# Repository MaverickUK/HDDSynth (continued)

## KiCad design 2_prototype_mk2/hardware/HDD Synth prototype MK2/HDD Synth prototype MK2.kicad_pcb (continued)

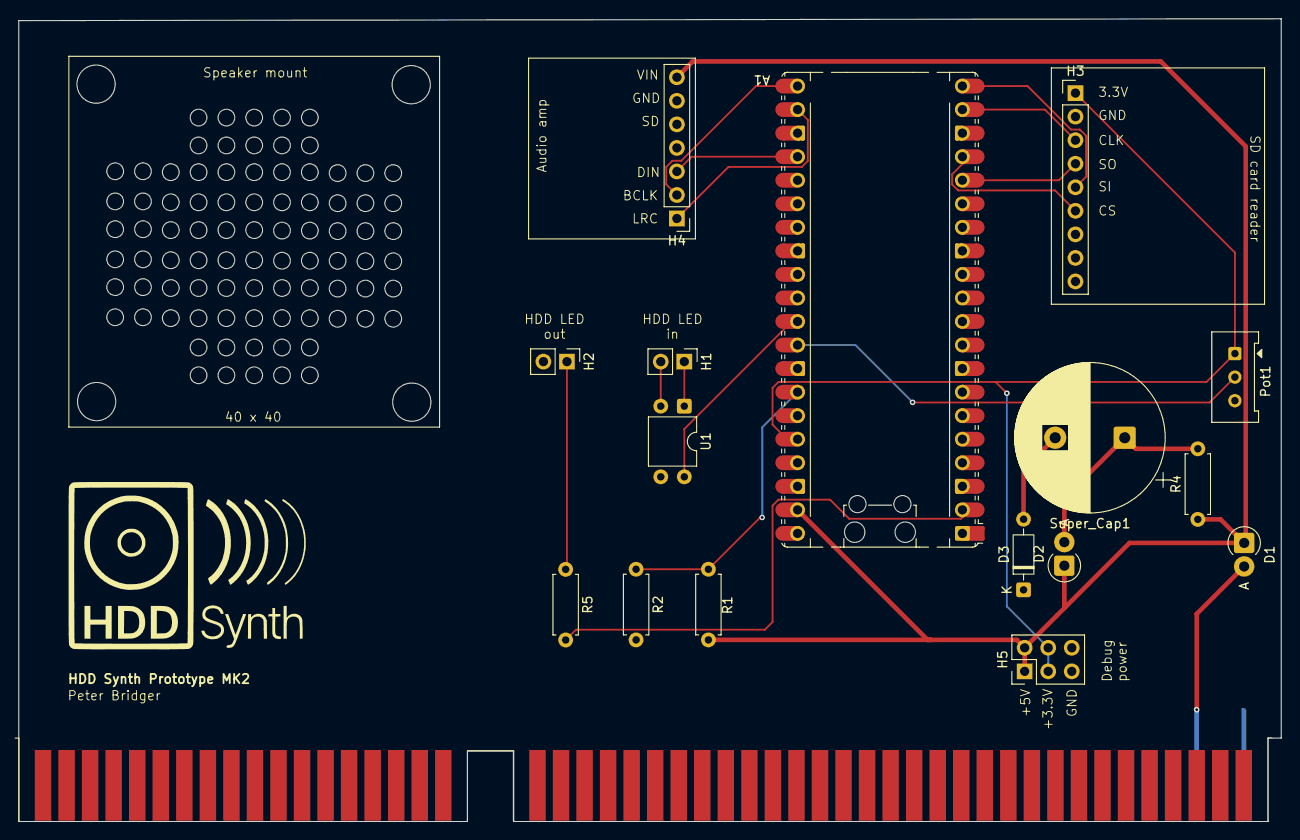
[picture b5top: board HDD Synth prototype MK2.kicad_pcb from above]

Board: 2 copper layers, 136.2 x 86.6 mm, 17 parts (0 on the bottom side), 19 nets.

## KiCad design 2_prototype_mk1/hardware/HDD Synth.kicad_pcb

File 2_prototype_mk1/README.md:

## HDD Synth
### Phase 2: PCB based prototypes

Phase 1 has established that this project is possible from both a hardware and software perspective. This phase is to create and iterate using a professionally manufactured PCB ready to enter phase 3, which will produce the released board.

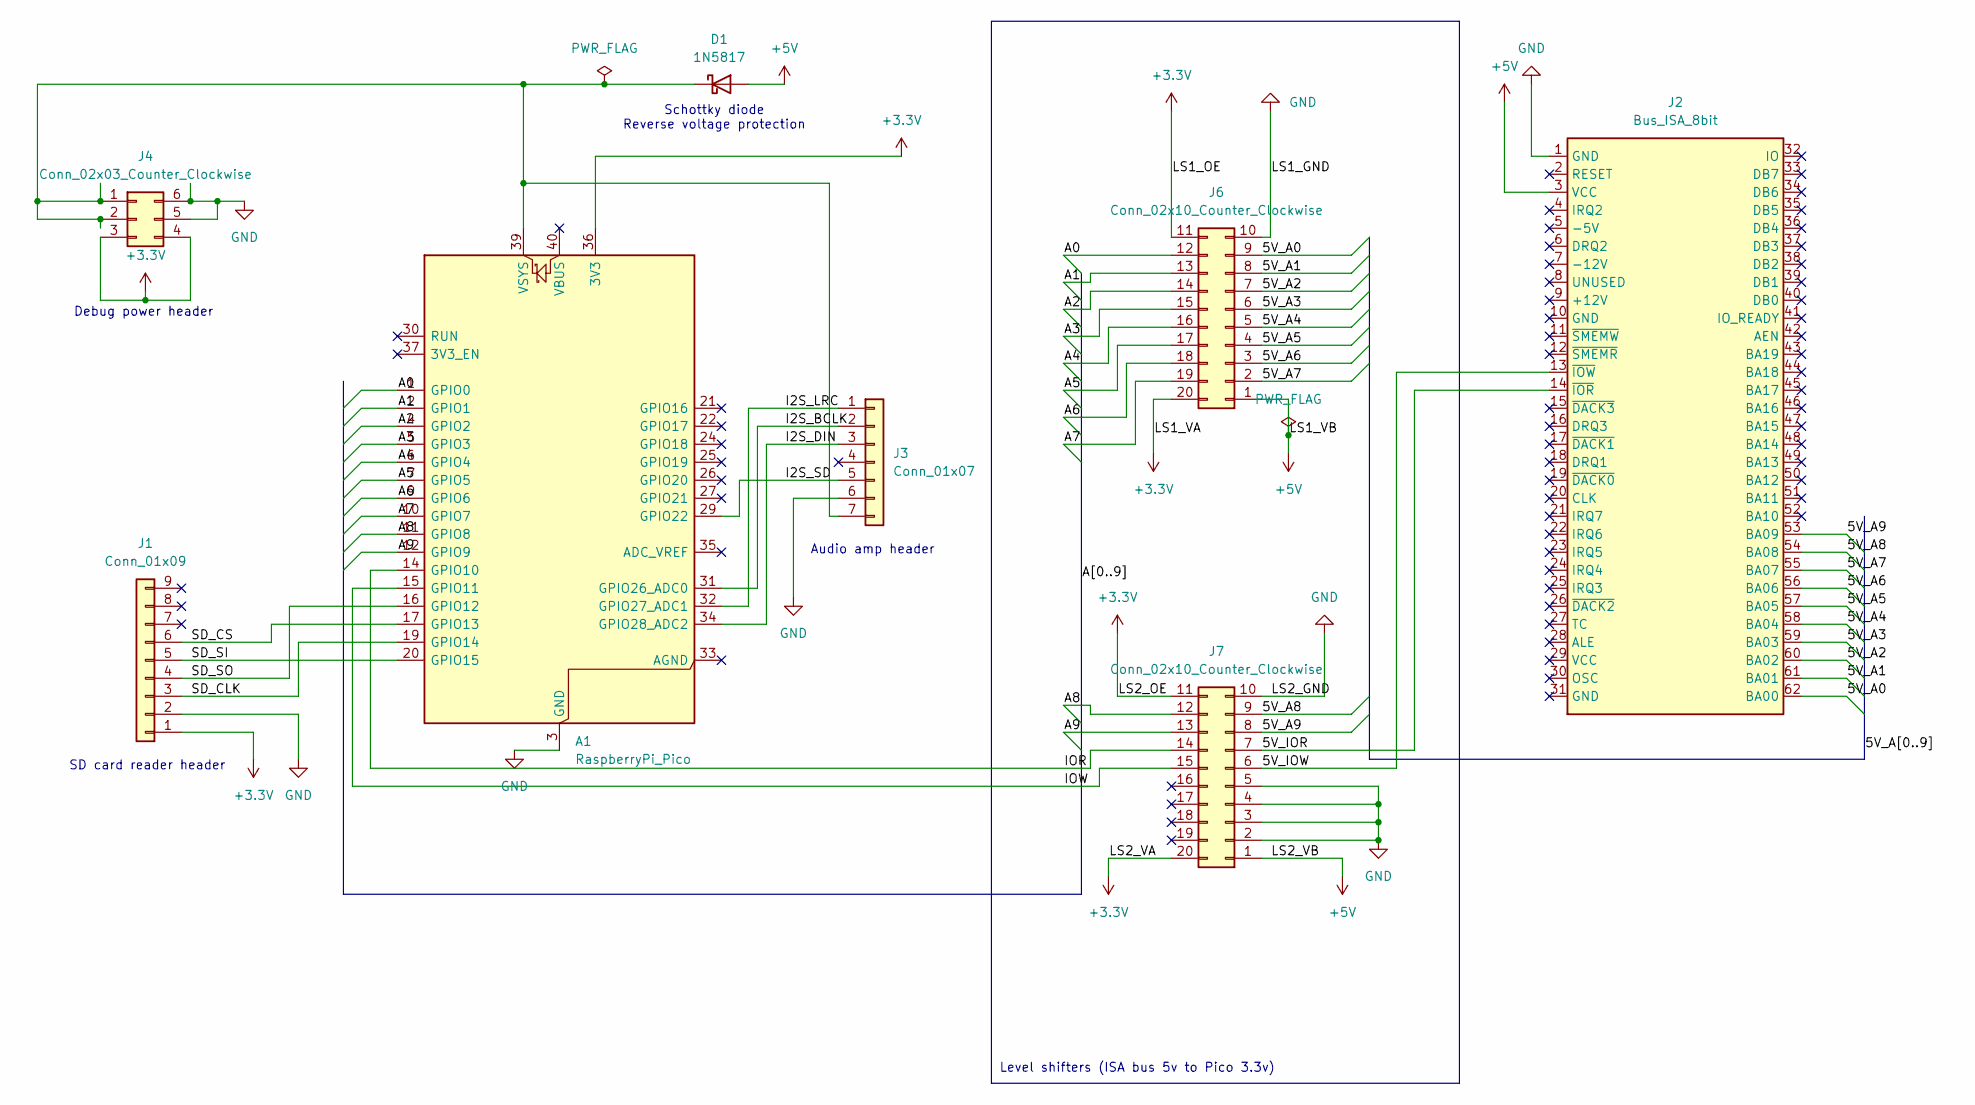
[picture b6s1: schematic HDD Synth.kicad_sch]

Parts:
A1: RaspberryPi_Pico; RaspberryPi_Pico_Common_Unspecified
D1: 1N5817; D_DO-41_SOD81_P2.54mm_Vertical_AnodeUp
J1: Conn_01x09; PinHeader_1x09_P2.54mm_Vertical
J2: Bus_ISA_8bit; BUS_AT
J3: Conn_01x07; PinHeader_1x07_P2.54mm_Vertical
J4: Conn_02x03_Counter_Clockwise; PinHeader_2x03_P2.54mm_Vertical
J6, J7: Conn_02x10_Counter_Clockwise; TXS0108E_2x10_Header2

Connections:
+3.3V: A1.36 (3V3), J1.1, J4.3, J4.4, J6.11, J6.20, J7.11, J7.20
+5V: D1.2 (A), J2.3 (VCC), J6.1, J7.1
/5V_A0: J2.62 (BA00), J6.9
/5V_A1: J2.61 (BA01), J6.8
/5V_A2: J2.60 (BA02), J6.7
/5V_A3: J2.59 (BA03), J6.6
/5V_A4: J2.58 (BA04), J6.5
/5V_A5: J2.57 (BA05), J6.4
/5V_A6: J2.56 (BA06), J6.3
/5V_A7: J2.55 (BA07), J6.2
/5V_A8: J2.54 (BA08), J7.9
/5V_A9: J2.53 (BA09), J7.8
/5V_IOR: J2.14 (~IOR), J7.7
/5V_IOW: J2.13 (~IOW), J7.6
/A0: A1.1 (GPIO0), J6.12
/A1: A1.2 (GPIO1), J6.13
/A2: A1.4 (GPIO2), J6.14
/A3: A1.5 (GPIO3), J6.15
/A4: A1.6 (GPIO4), J6.16
/A5: A1.7 (GPIO5), J6.17
/A6: A1.9 (GPIO6), J6.18
/A7: A1.10 (GPIO7), J6.19
/A8: A1.11 (GPIO8), J7.12
/A9: A1.12 (GPIO9), J7.13
/I2S_BCLK: A1.31 (GPIO26_ADC0), J3.2
/I2S_DIN: A1.34 (GPIO28_ADC2), J3.3
/I2S_LRC: A1.32 (GPIO27_ADC1), J3.1
/I2S_SD: A1.29 (GPIO22), J3.5
/IOR: A1.14 (GPIO10), J7.14
/IOW: A1.15 (GPIO11), J7.15
/SD_CLK: A1.19 (GPIO14), J1.3
/SD_CS: A1.17 (GPIO13), J1.6
/SD_SI: A1.20 (GPIO15), J1.5
/SD_SO: A1.16 (GPIO12), J1.4
GND: A1.3 (GND), A1.8 (GND), A1.13 (GND), A1.18 (GND), A1.23 (GND), A1.28 (GND), A1.38 (GND), J1.2, J2.1 (GND), J3.6, J4.5, J4.6, J6.10, J7.2, J7.3, J7.4, J7.5, J7.10
unnamed: A1.39 (VSYS), D1.1 (K), J3.7, J4.1, J4.2

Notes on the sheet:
Debug power header
SD card reader header
Level shifters (ISA bus 5v to Pico 3.3v)
Schottky diode Reverse voltage protection
Audio amp header

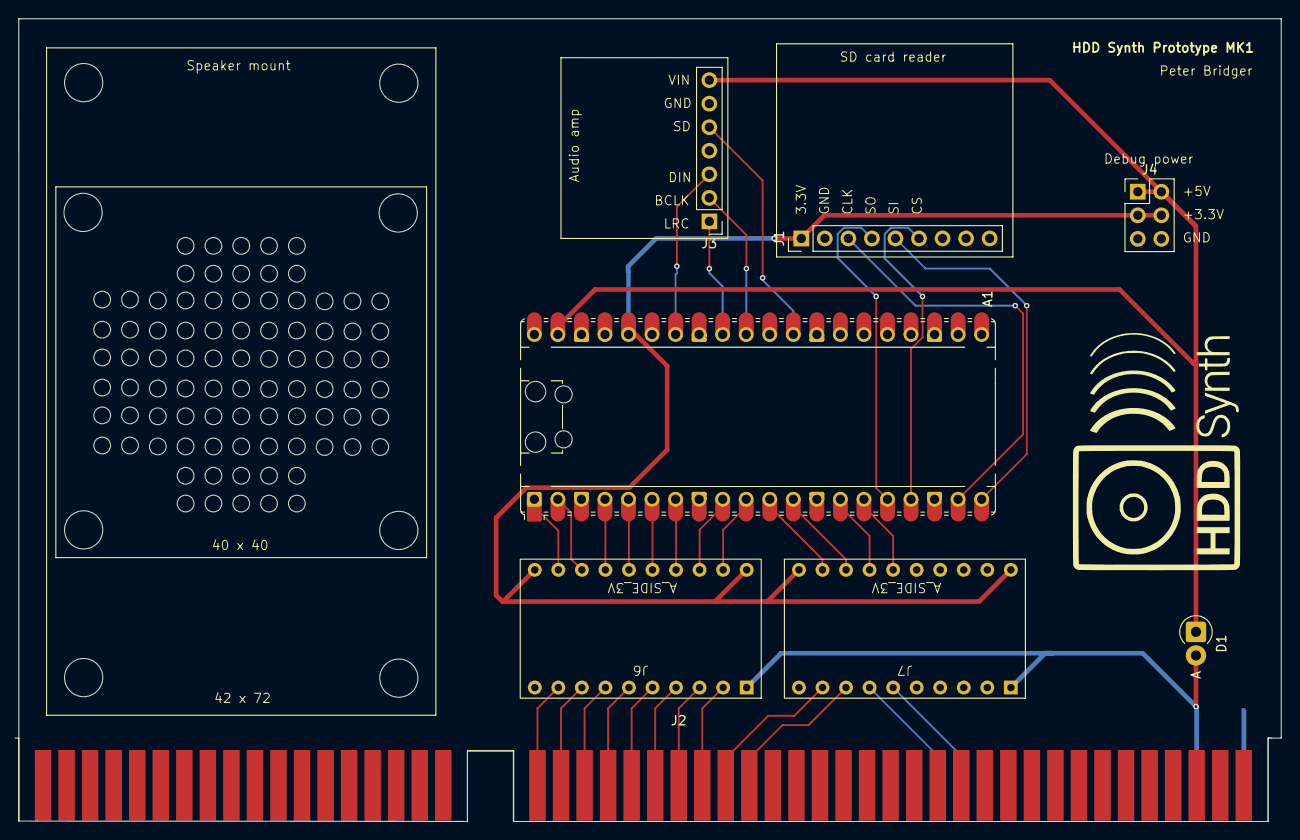
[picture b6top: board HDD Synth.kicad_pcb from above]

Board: 2 copper layers, 136.2 x 86.6 mm, 8 parts (0 on the bottom side), 36 nets.

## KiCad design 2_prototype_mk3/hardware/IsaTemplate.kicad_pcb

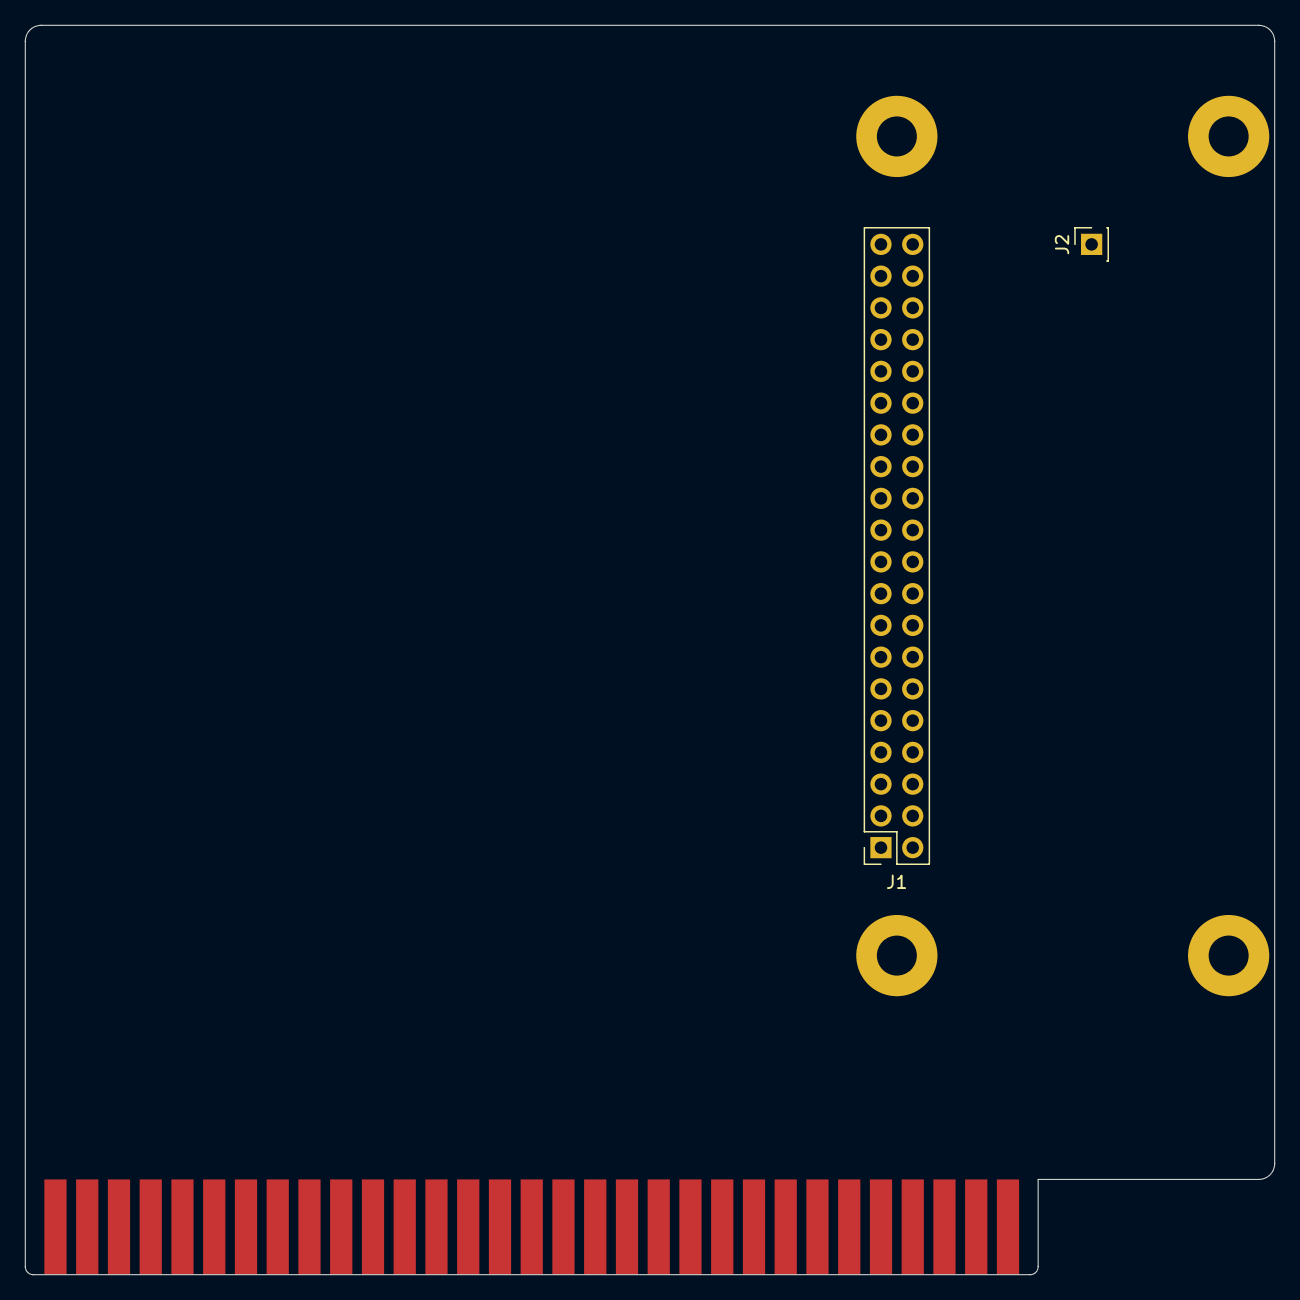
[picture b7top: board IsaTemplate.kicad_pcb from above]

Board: 2 copper layers, 99.9 x 99.9 mm, 7 parts (0 on the bottom side), 2 nets, no tracks yet.

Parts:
H1, H2, H3, H4: MountingHole_Pad; MountingHole_3.5mm_Pad
J1: IDE_CONNECTOR; PinSocket_2x20_P2.54mm_Vertical
J2: CF Adapter Power; PinSocket_1x01_P2.54mm_Vertical
J3: Bus_ISA_8bit; BUS_XT

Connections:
GND: J3.1, J3.10, J3.31
VCC: J2.1, J3.3, J3.29

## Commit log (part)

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2025-08-03 WIP from Pico
    Files taken from Pico before revisiting the project
2025-08-03 Refresh README with new logo and latest media
2025-08-04 Expand acknowledgments
2025-08-04 Extend scope to include floppy drive controller
2025-08-04 Ensure that the logo is always shown on a white background
2025-08-04 Add descriptions to media
2025-08-05 Create isa_monitor.py
    PIO approach
2025-08-05 Update isa_monitor.py
    State machine encoding information
2025-08-05 Update audio_mixer.py
    Include stop method
2025-08-05 Update main.py
    Run idle HDD with random access requests whilst mixing in keyboard sounds
2025-08-05 Update main.py
    Add detailed comments
2025-08-05 Update handler.py
    Output information about the type of IO activity detected
2025-08-17 Create circuitpython_hdd_basic.py
    A working prototype of HDD Synth using voltage detection of the HDD LED line
2025-08-17 Clean up and incorporate work done directly on Pico into repository
2025-08-17 Refactoring
2025-08-18 Convert to CircuitPython to make use of better audio libraries
2025-08-18 Reintroduce threshold detection for ISA HDD activity
2025-08-18 Replace legacy MicroPython main file with CircuitPython
2025-08-18 CircuitPython approach POC tests
2025-08-21 Reorgnaise project into phases
2025-08-21 Add prototype board image
2025-08-21 Fix missing space
2025-08-23 Update PCB prototype photo
2025-10-12 Add KiCad hardware files for prototype MK1
2025-10-12 Update prototype MK1 readme with details of MK2 direction
2026-02-26 Working MKII implementation
2026-02-26 Add Sync to Pico script
2026-03-01 Improvements
    - Improve beep to sound more pleasing (Use sin or triangle waveform)
    - Allow external power detection to be disabled
    - Move access detection hold time to settings and increase to 100ms
2026-03-01 Improvements
    - Nicer sounding beeps (Sin/trinagle wave instead of square wave)
    - Option to disable external power detection
    - Tweaked activity detection to sound better
2026-03-05 Multiple refinements and new features
2026-03-22 Add Prototype MKIII designs
2026-03-24 MKIII design refinements
2026-04-12 Add net classes for power
2026-04-12 MKIII PCB components connected and passing DRC
2026-04-13 Switch to GPLv3 licence
2026-04-13 Finalise silk screen and tidy up files
2026-04-13 Remove .DS_Store files and ignore them
2026-04-13 Tweak git ignore
2026-04-13 Add manufacturer part nu bers
2026-04-13 Switch SD card reader to better component
2026-04-13 Fix DRC issues and change SD card to injection model
2026-04-13 Improve ground connections
2026-04-13 Add LCSC component part numbers to BOM
2026-04-13 Add LCSC components part numbers
2026-04-13 Add LCSC component part numbers
2026-04-21 Created FDD connections to Pico and other key components
2026-05-05 MK4 prototype initial work
2026-05-06 Create initial MK4 PCB layout
2026-05-10 Placed all components on PCB
2026-05-10 Fixed all Electrical Rule Check errors
2026-05-17 MK4 PCB layout complete
2026-05-19 Final design to sent to PCBWay
2026-06-01 Update MKIV hardware & use MKIII software as basic for MKIV
2026-06-01 Volume to use rotatry encoder, not pot
2026-06-01 Refactor action button to move consts into settings.py
2026-06-01 Add balance mode to rotary encoder
2026-06-01 Save volume/balance settings to NVM after debounce period
2026-06-01 Large number of refactorings and minor bug fixes
2026-06-02 Gracefully handle first boot, when NVM isn't defined
2026-06-02 Gracefully handle missing jingle
2026-06-02 Clear cache directory before copying files into it
2026-06-09 Final MKIV tweaks before sending off to PCBWay
2026-06-09 Add spindown and idle sound playback settings
2026-06-09 Allow override settings to be loaded from SD card in settings.json file
2026-06-09 Fix issues when loading SD card settings file
2026-06-09 Remove unneeded test files
2026-06-09 Make volume control more granular
2026-06-09 Allow the HDD Synth to run without SD card being required (if sample pack is installed)
2026-06-09 Ensure NO_SD_CARD beep doesn't play when perform SD card init, as this is taken care of later
2026-06-09 Make SIMLUATION_MODE an SD card setting
2026-06-09 Fix the activity GPIO pin setting
2026-06-15 Update READMEs across the project
2026-06-15 Clean up
2026-06-15 MKIV add RGB LED, reset jumper and fixed reset circuit
2026-06-16 Make device select text consistent and correct
2026-06-16 Upgrade to use optimized SD card library - allows use of streaming samples from the SD card
2026-06-16 Pico sync script to use a relative path
2026-06-16 Optimise sample memory usage when running in SD card streaming mode
2026-06-16 MKIV tweaks
2026-06-16 Tweak
2026-06-17 MKV design start
2026-06-18 MKV - SATA connector and wiring complete
2026-06-18 Hide speaker mount refs + create 3D model
2026-06-21 Major MKV redesign using embedded RP2350
2026-06-30 MKV: Add LCSC numbers and resolve DRC errors
